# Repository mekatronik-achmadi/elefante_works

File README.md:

# elefante_works
Collection of my works on Elefante

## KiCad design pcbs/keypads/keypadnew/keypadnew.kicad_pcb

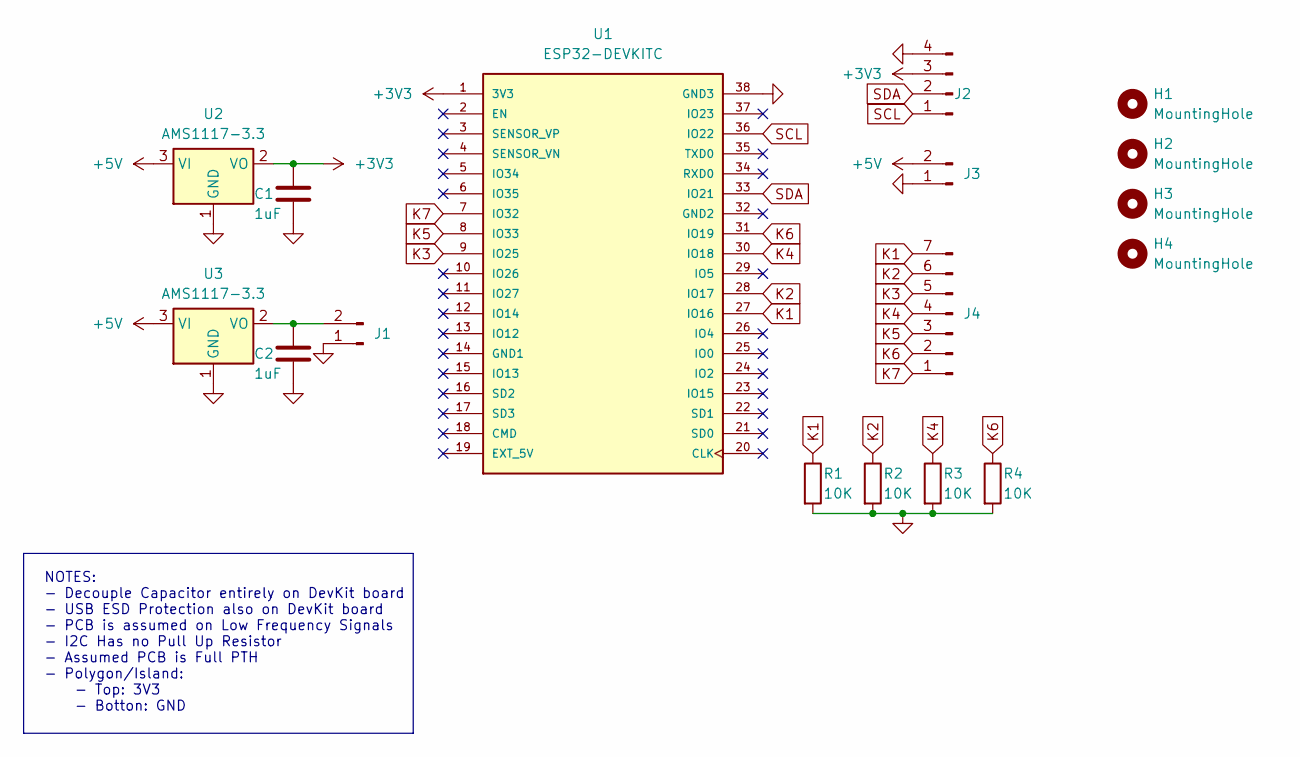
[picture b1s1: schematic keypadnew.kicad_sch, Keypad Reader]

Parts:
C1, C2: 1uF; C_1206_3216Metric_Pad1.33x1.80mm_HandSolder
H1, H2, H3, H4: MountingHole; MountingHole_2.1mm
J1, J3: Conn_01x02_Pin; PinHeader_1x02_P2.54mm_Horizontal
J2: Conn_01x04_Pin; PinHeader_1x04_P2.54mm_Horizontal
J4: Conn_01x07_Pin; PinHeader_1x07_P2.54mm_Horizontal
R1, R2, R3, R4: 10K; R_1206_3216Metric_Pad1.30x1.75mm_HandSolder
U1: ESP32-DEVKITC; MODULE_ESP32-DEVKITC; PARTREV N/A
U2, U3: AMS1117-3.3; SOT-223-3_TabPin2

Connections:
+3V3: C1.1, J2.3, U1.1 (3V3), U2.2 (VO)
+5V: J3.2, U2.3 (VI), U3.3 (VI)
GND: C1.2, C2.2, J1.1, J2.4, J3.1, R1.2, R2.2, R3.2, R4.2, U1.38 (GND3), U2.1 (GND), U3.1 (GND)
K1: J4.7, R1.1, U1.27 (IO16)
K2: J4.6, R2.1, U1.28 (IO17)
K3: J4.5, U1.9 (IO25)
K4: J4.4, R3.1, U1.30 (IO18)
K5: J4.3, U1.8 (IO33)
K6: J4.2, R4.1, U1.31 (IO19)
K7: J4.1, U1.7 (IO32)
unnamed: C2.1, J1.2, U3.2 (VO)
SCL: J2.1, U1.36 (IO22)
SDA: J2.2, U1.33 (IO21)

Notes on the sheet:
NOTES: - Decouple Capacitor entirely on DevKit board - USB ESD Protection also on DevKit board - PCB is assumed on Low Frequency Signals - I2C Has no Pull Up Resistor - Assumed PCB is Full PTH - Polygon/Island: - Top: 3V3 - Botton: GND

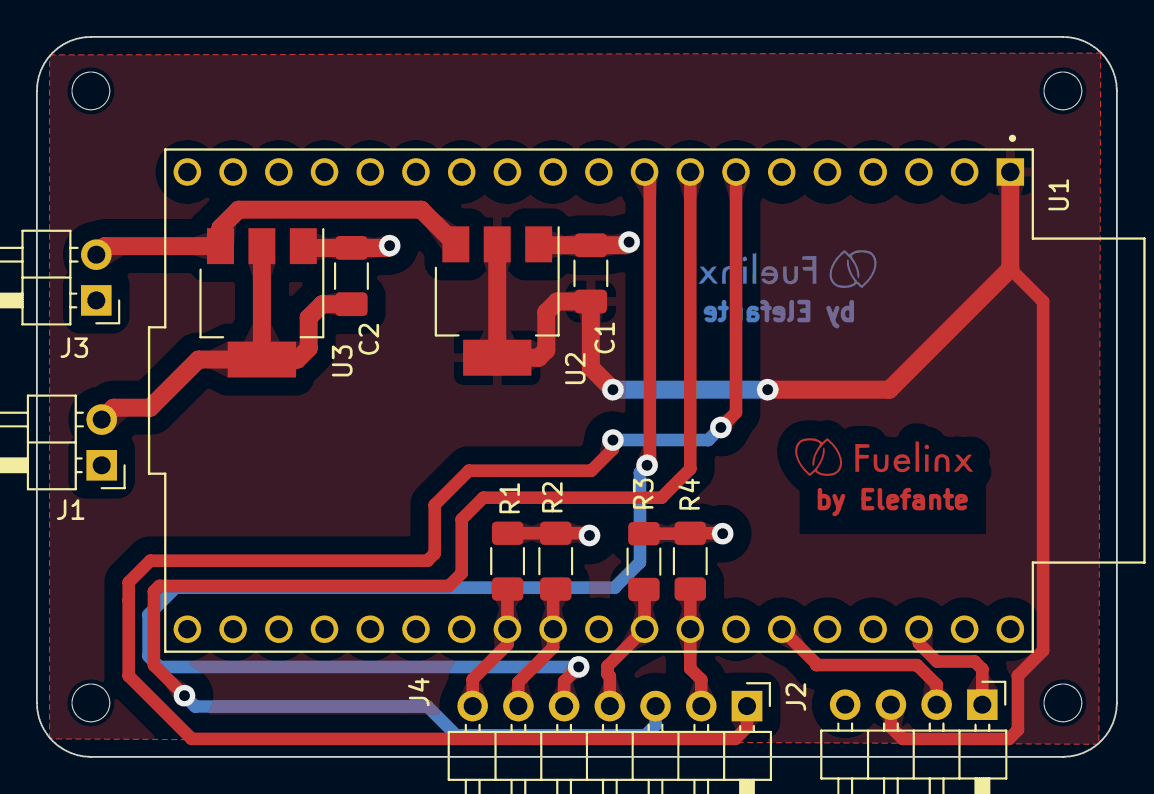
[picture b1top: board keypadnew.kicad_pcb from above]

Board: 2 copper layers, 60.0 x 40.0 mm, 17 parts (0 on the bottom side), 13 nets.

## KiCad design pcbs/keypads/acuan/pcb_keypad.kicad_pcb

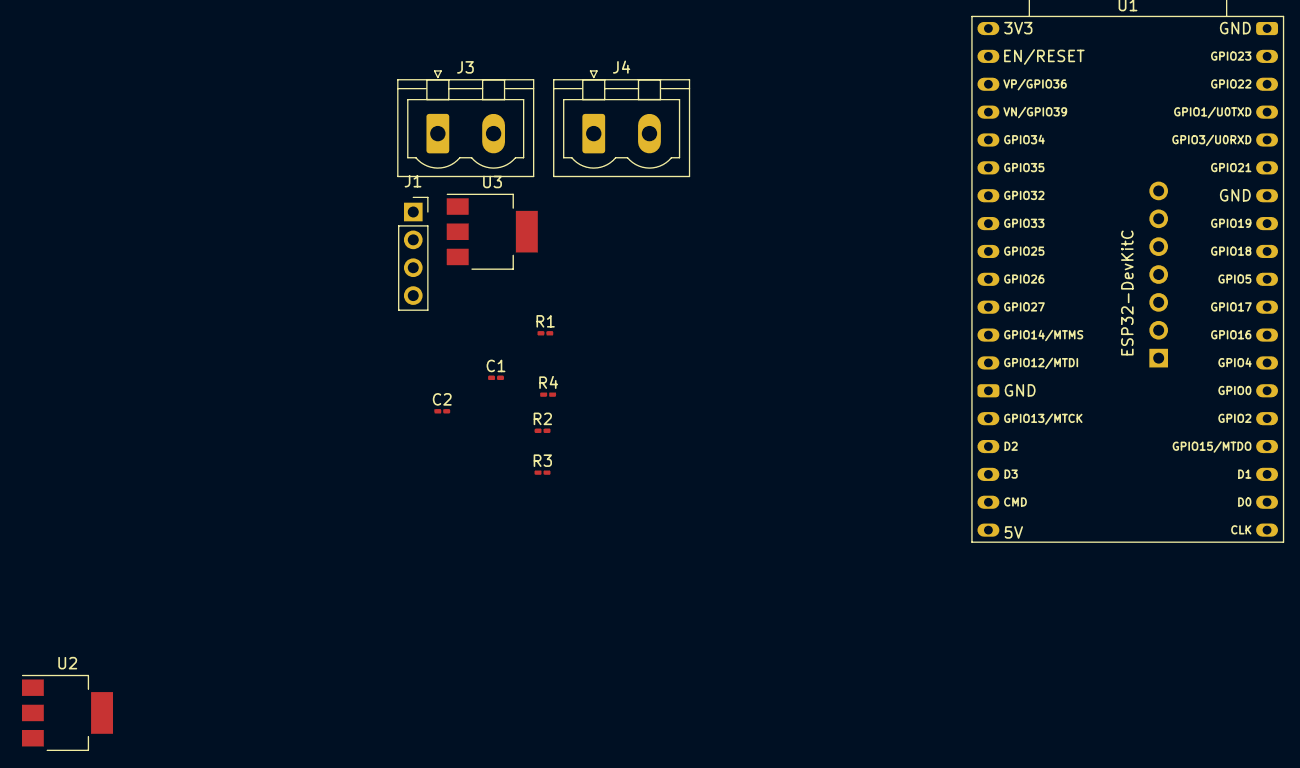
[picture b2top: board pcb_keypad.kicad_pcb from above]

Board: 2 copper layers, 13 parts (1 on the bottom side), 13 nets, no tracks yet.

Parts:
C1, C2: C; C_0201_0603Metric_Pad0.64x0.40mm_HandSolder
J1: i2c_LCD; PinSocket_1x04_P2.54mm_Vertical
J2: Keypad_pin; PinSocket_1x07_P2.54mm_Vertical
J3, J4: powerConnector; PhoenixContact_MSTBVA_2,5_2-G-5,08_1x02_P5.08mm_Vertical
R1, R2, R3, R4: 10k; R_0201_0603Metric_Pad0.64x0.40mm_HandSolder
U1: ESP32-DevKitC
U2: ams_esp; SOT-223-3_TabPin2
U3: ams_lain; SOT-223-3_TabPin2

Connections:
/3v3: C2.1, J1.2, U1.1 (3V3), U2.2 (VO)
/5v: J3.1, U2.3 (VI), U3.3 (VI)
/gnd: C1.2, C2.2, J1.1, J3.2, J4.2, R1.2, R2.2, R3.2, R4.2, U1.38 (GND), U2.1 (GND), U3.1 (GND)
/k1: J2.1, R1.1, U1.27 (GPIO16)
/k2: J2.2, R2.1, U1.28 (GPIO17)
/k3: J2.3, U1.9 (DAC_1/ADC2_CH8/GPIO25)
/k4: J2.4, R3.1, U1.30 (GPIO18)
/k5: J2.5, U1.8 (32K_XN/GPIO33/ADC1_CH5)
/k6: J2.6, R4.1, U1.31 (GPIO19)
/k7: J2.7, U1.7 (32K_XP/GPIO32/ADC1_CH4)
/scl: J1.4, U1.36 (GPIO22)
/sda: J1.3, U1.33 (GPIO21)
unnamed: C1.1, J4.1, U3.2 (VO)

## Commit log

2023-11-08 Initial works
2023-11-08 Keypad Reader
2023-11-08 Keypad Reader PCB
2023-11-08 Update PCB Keypad Reader
2023-11-08 Logo di PCB
